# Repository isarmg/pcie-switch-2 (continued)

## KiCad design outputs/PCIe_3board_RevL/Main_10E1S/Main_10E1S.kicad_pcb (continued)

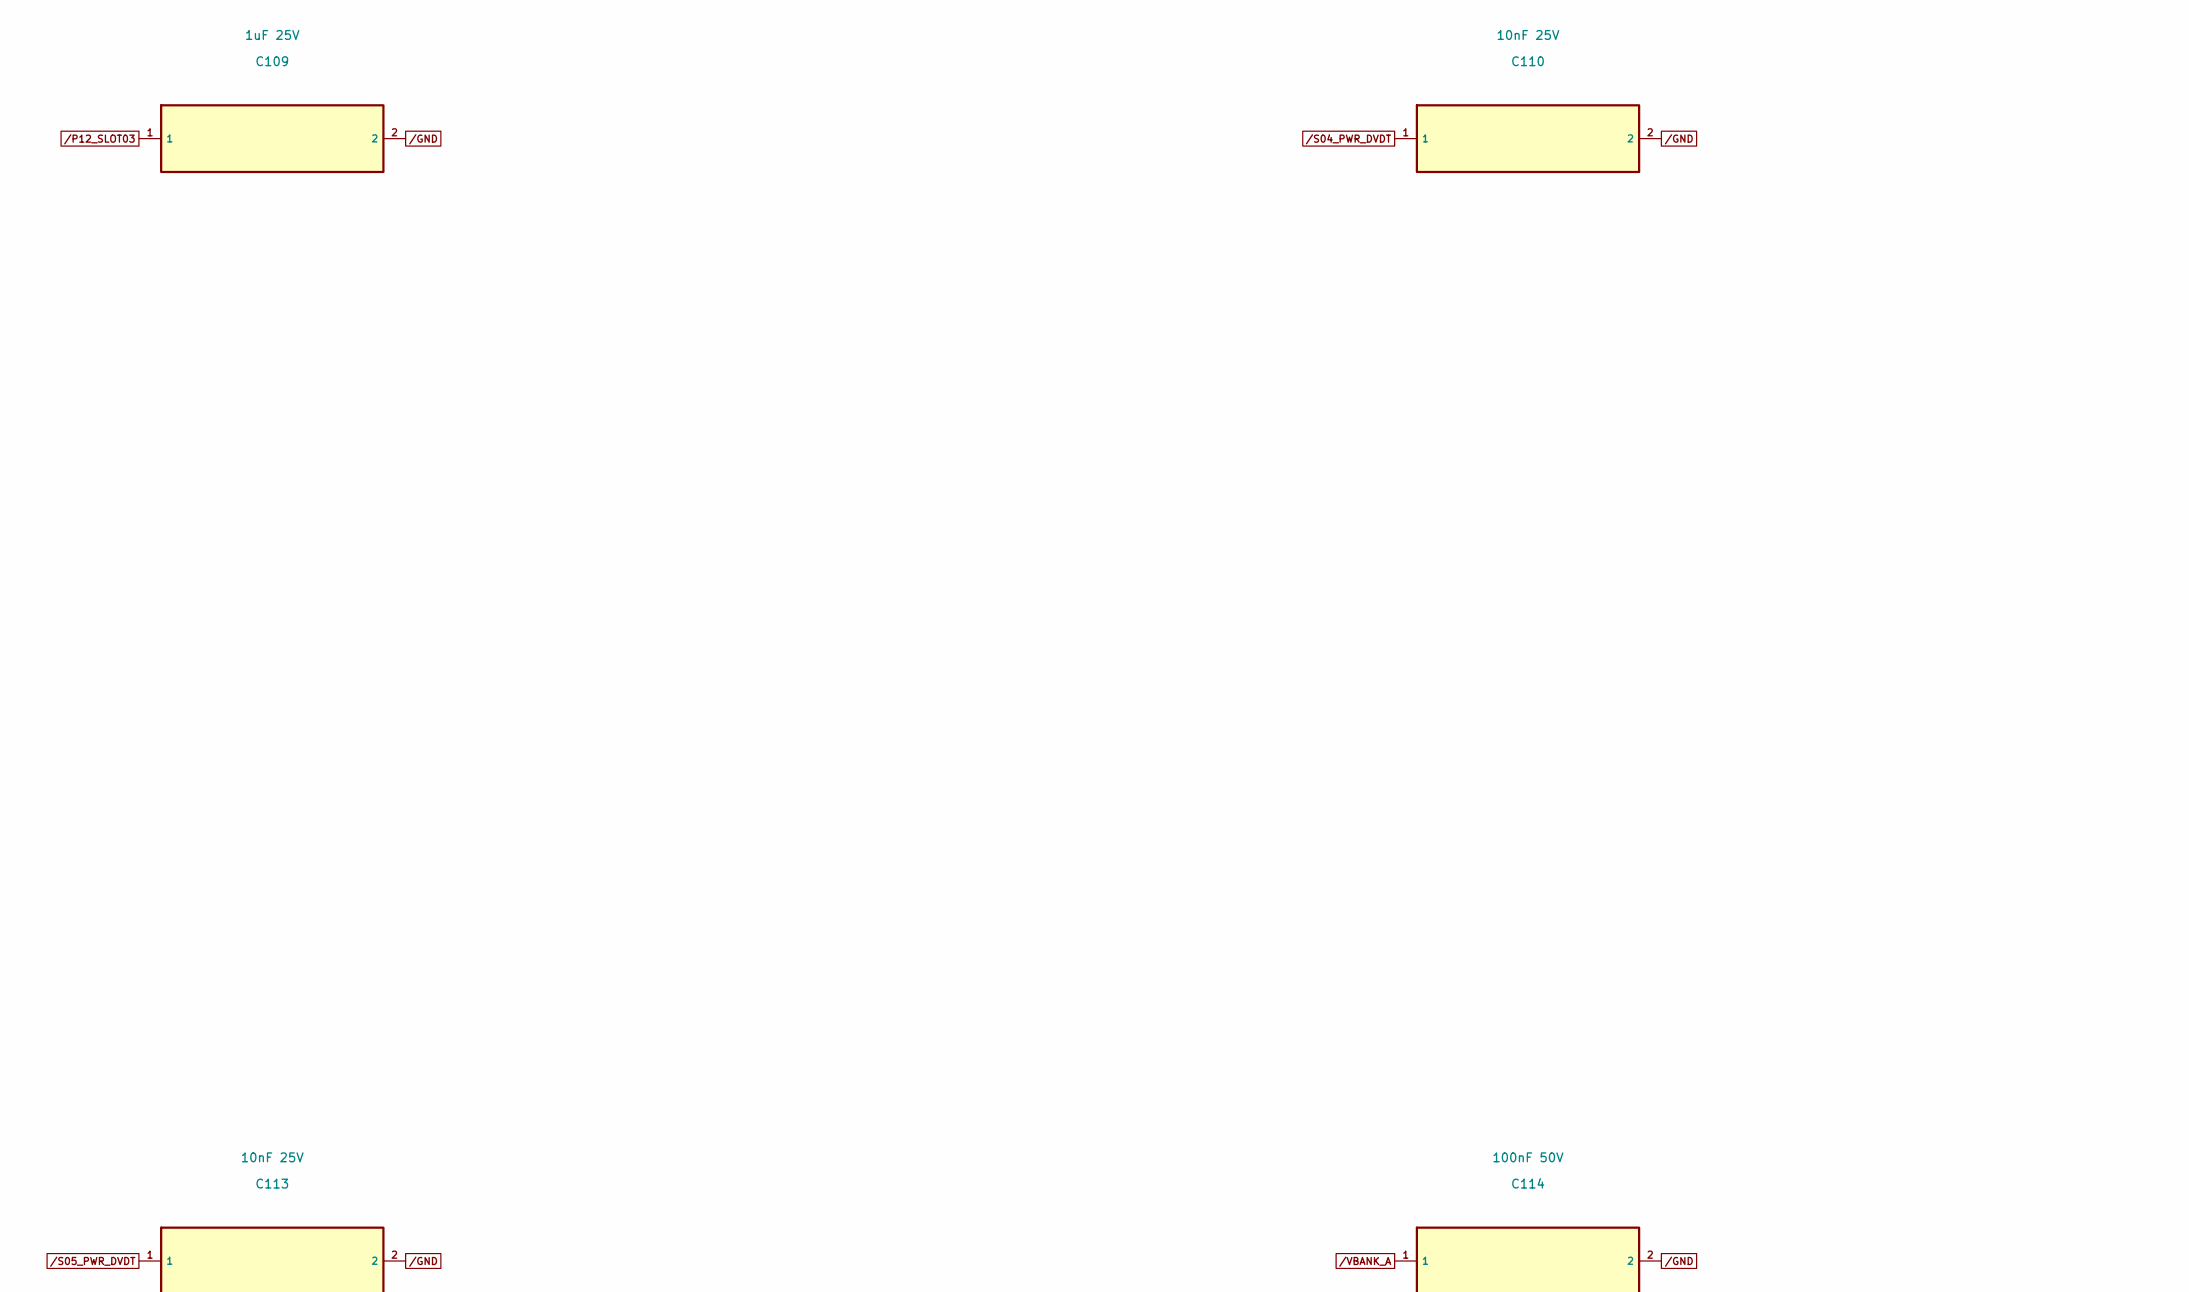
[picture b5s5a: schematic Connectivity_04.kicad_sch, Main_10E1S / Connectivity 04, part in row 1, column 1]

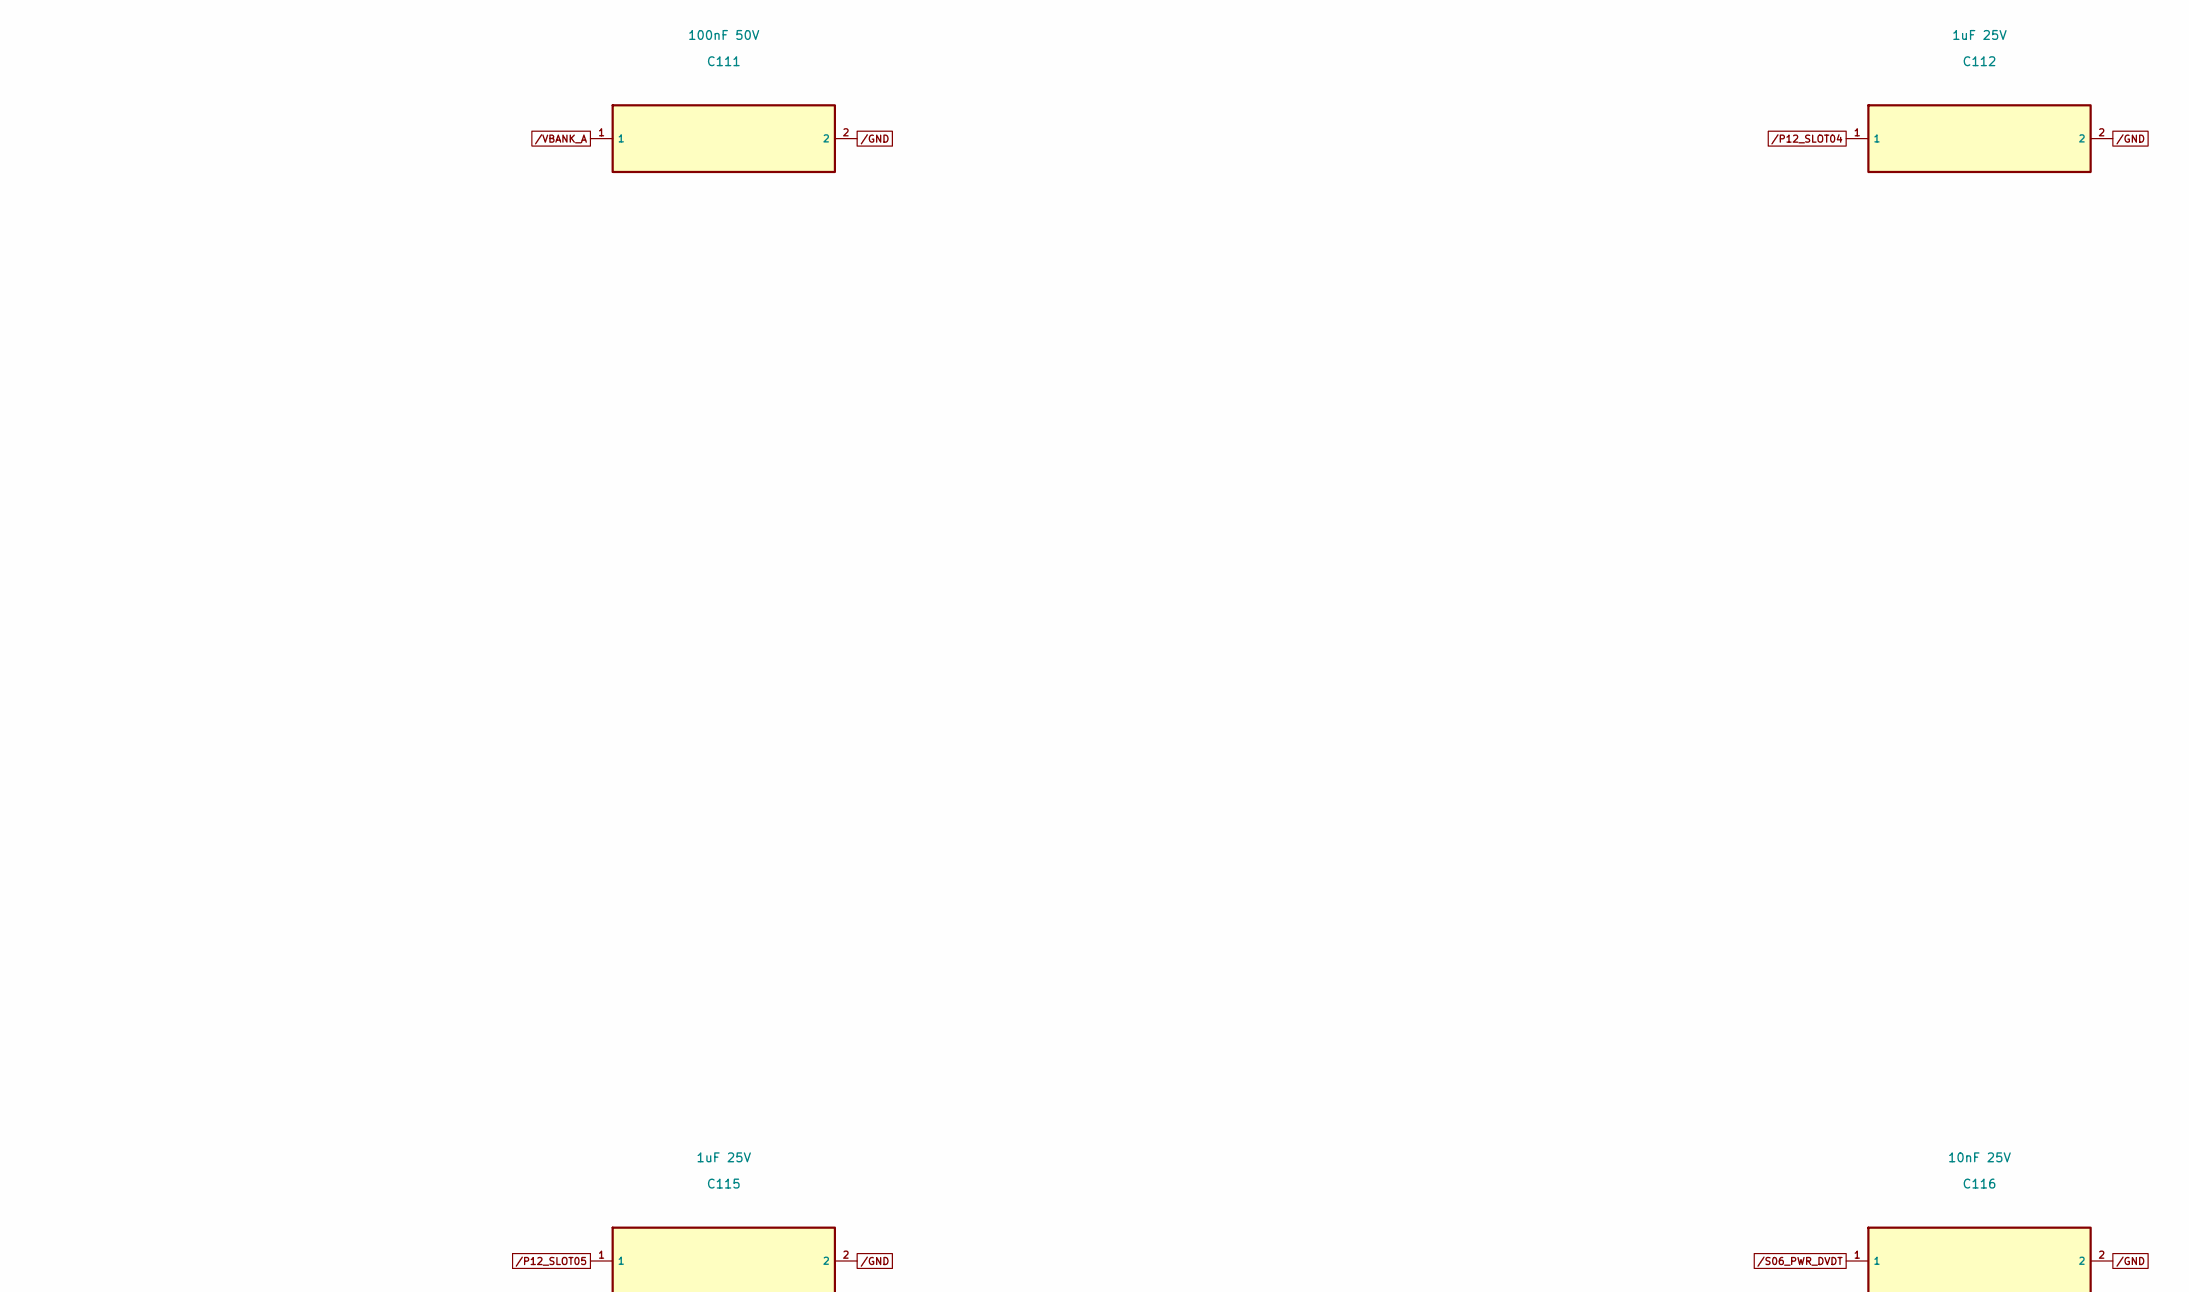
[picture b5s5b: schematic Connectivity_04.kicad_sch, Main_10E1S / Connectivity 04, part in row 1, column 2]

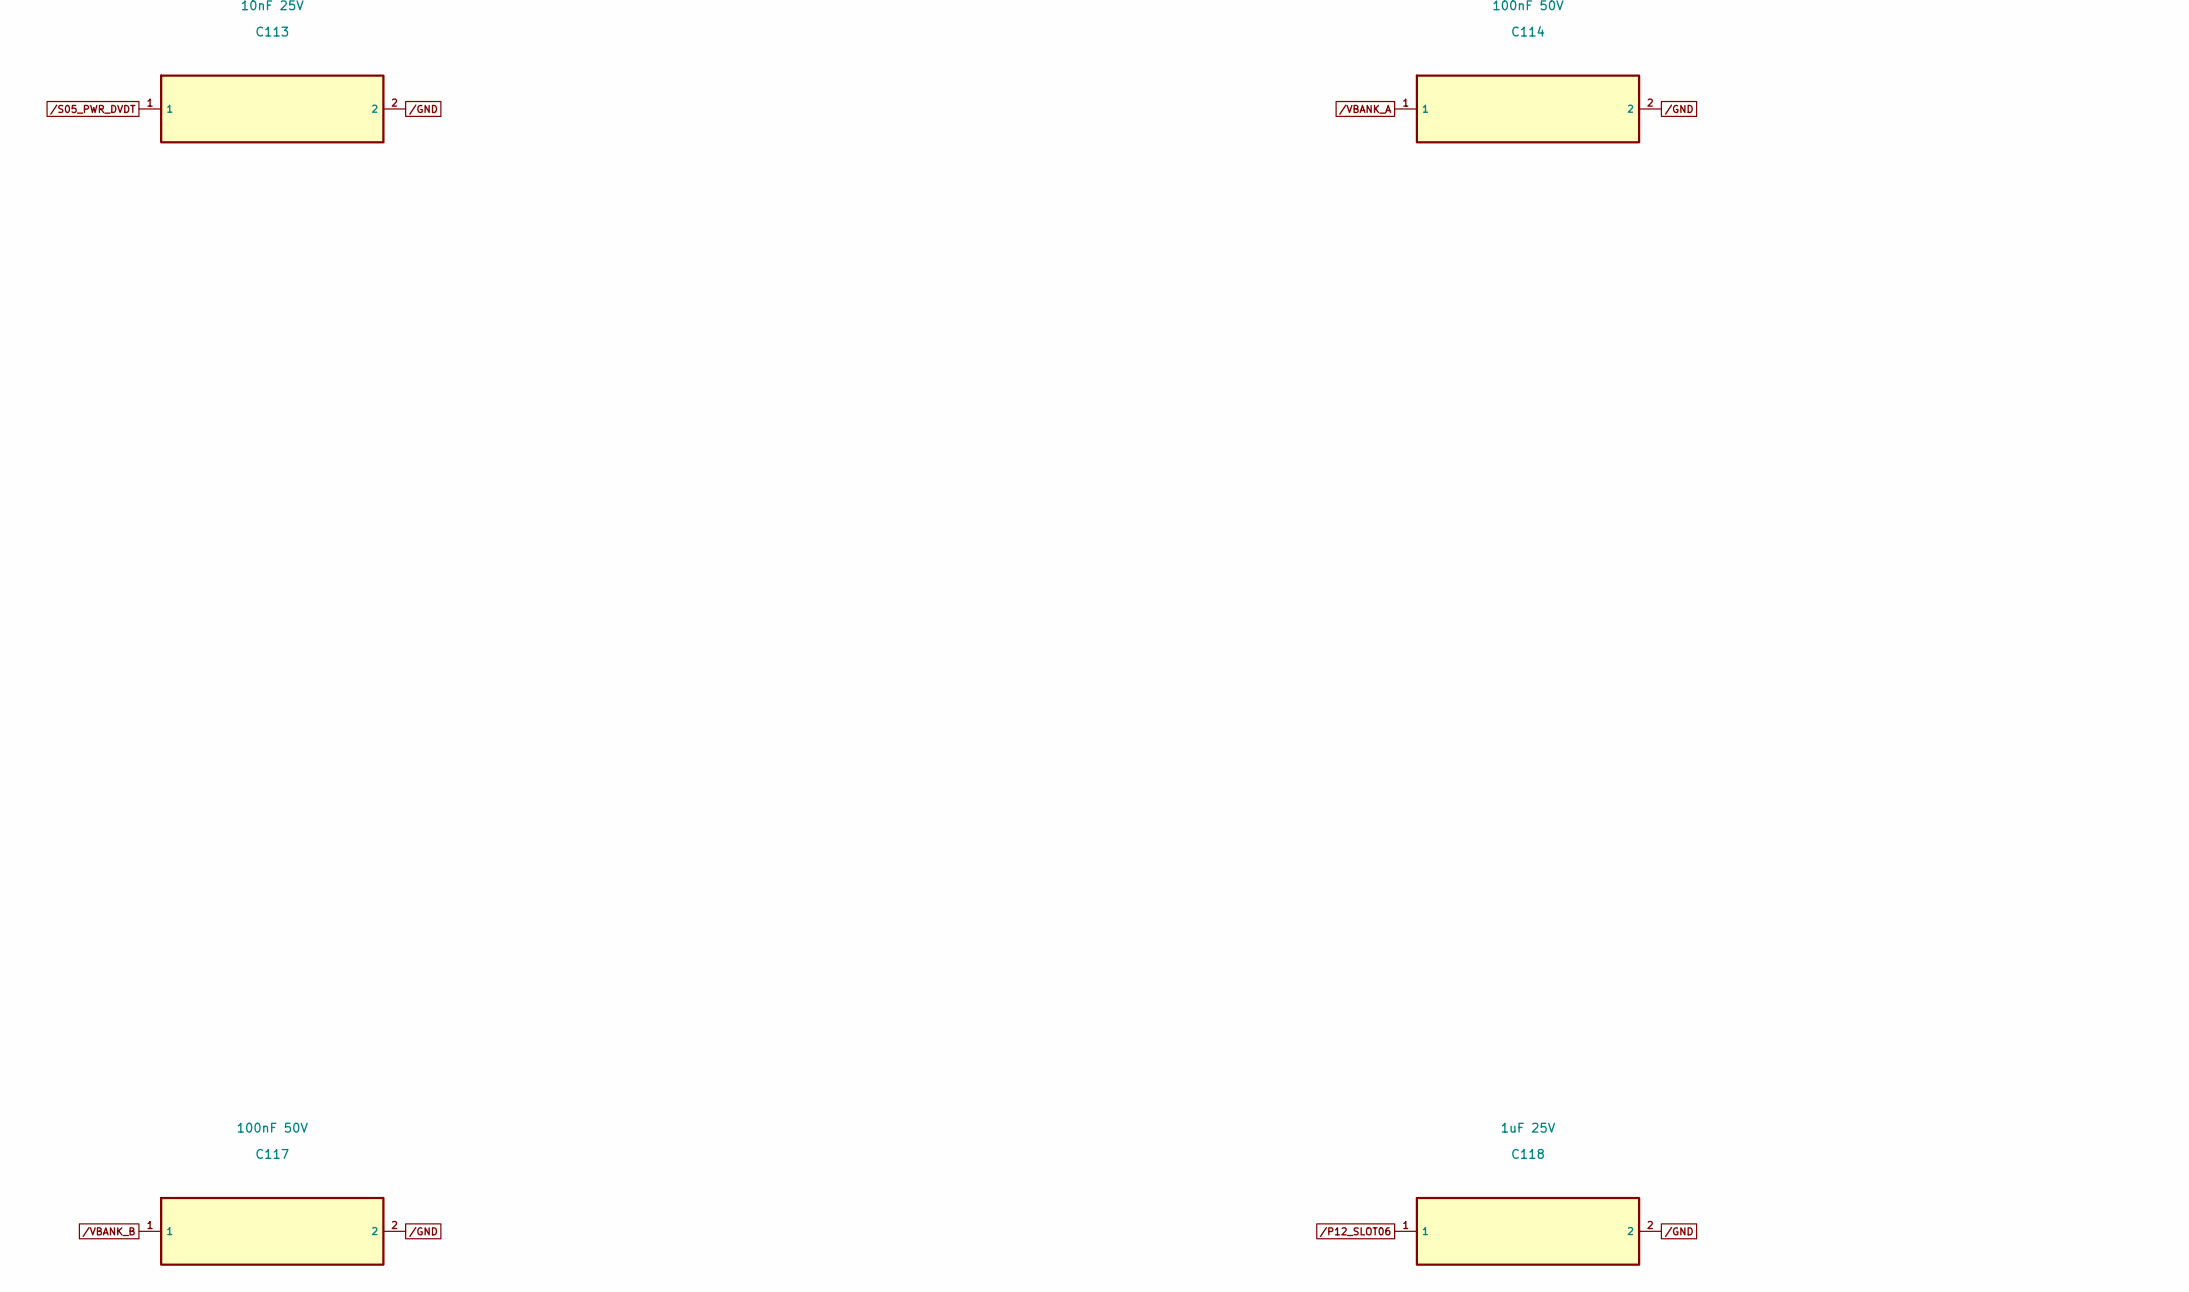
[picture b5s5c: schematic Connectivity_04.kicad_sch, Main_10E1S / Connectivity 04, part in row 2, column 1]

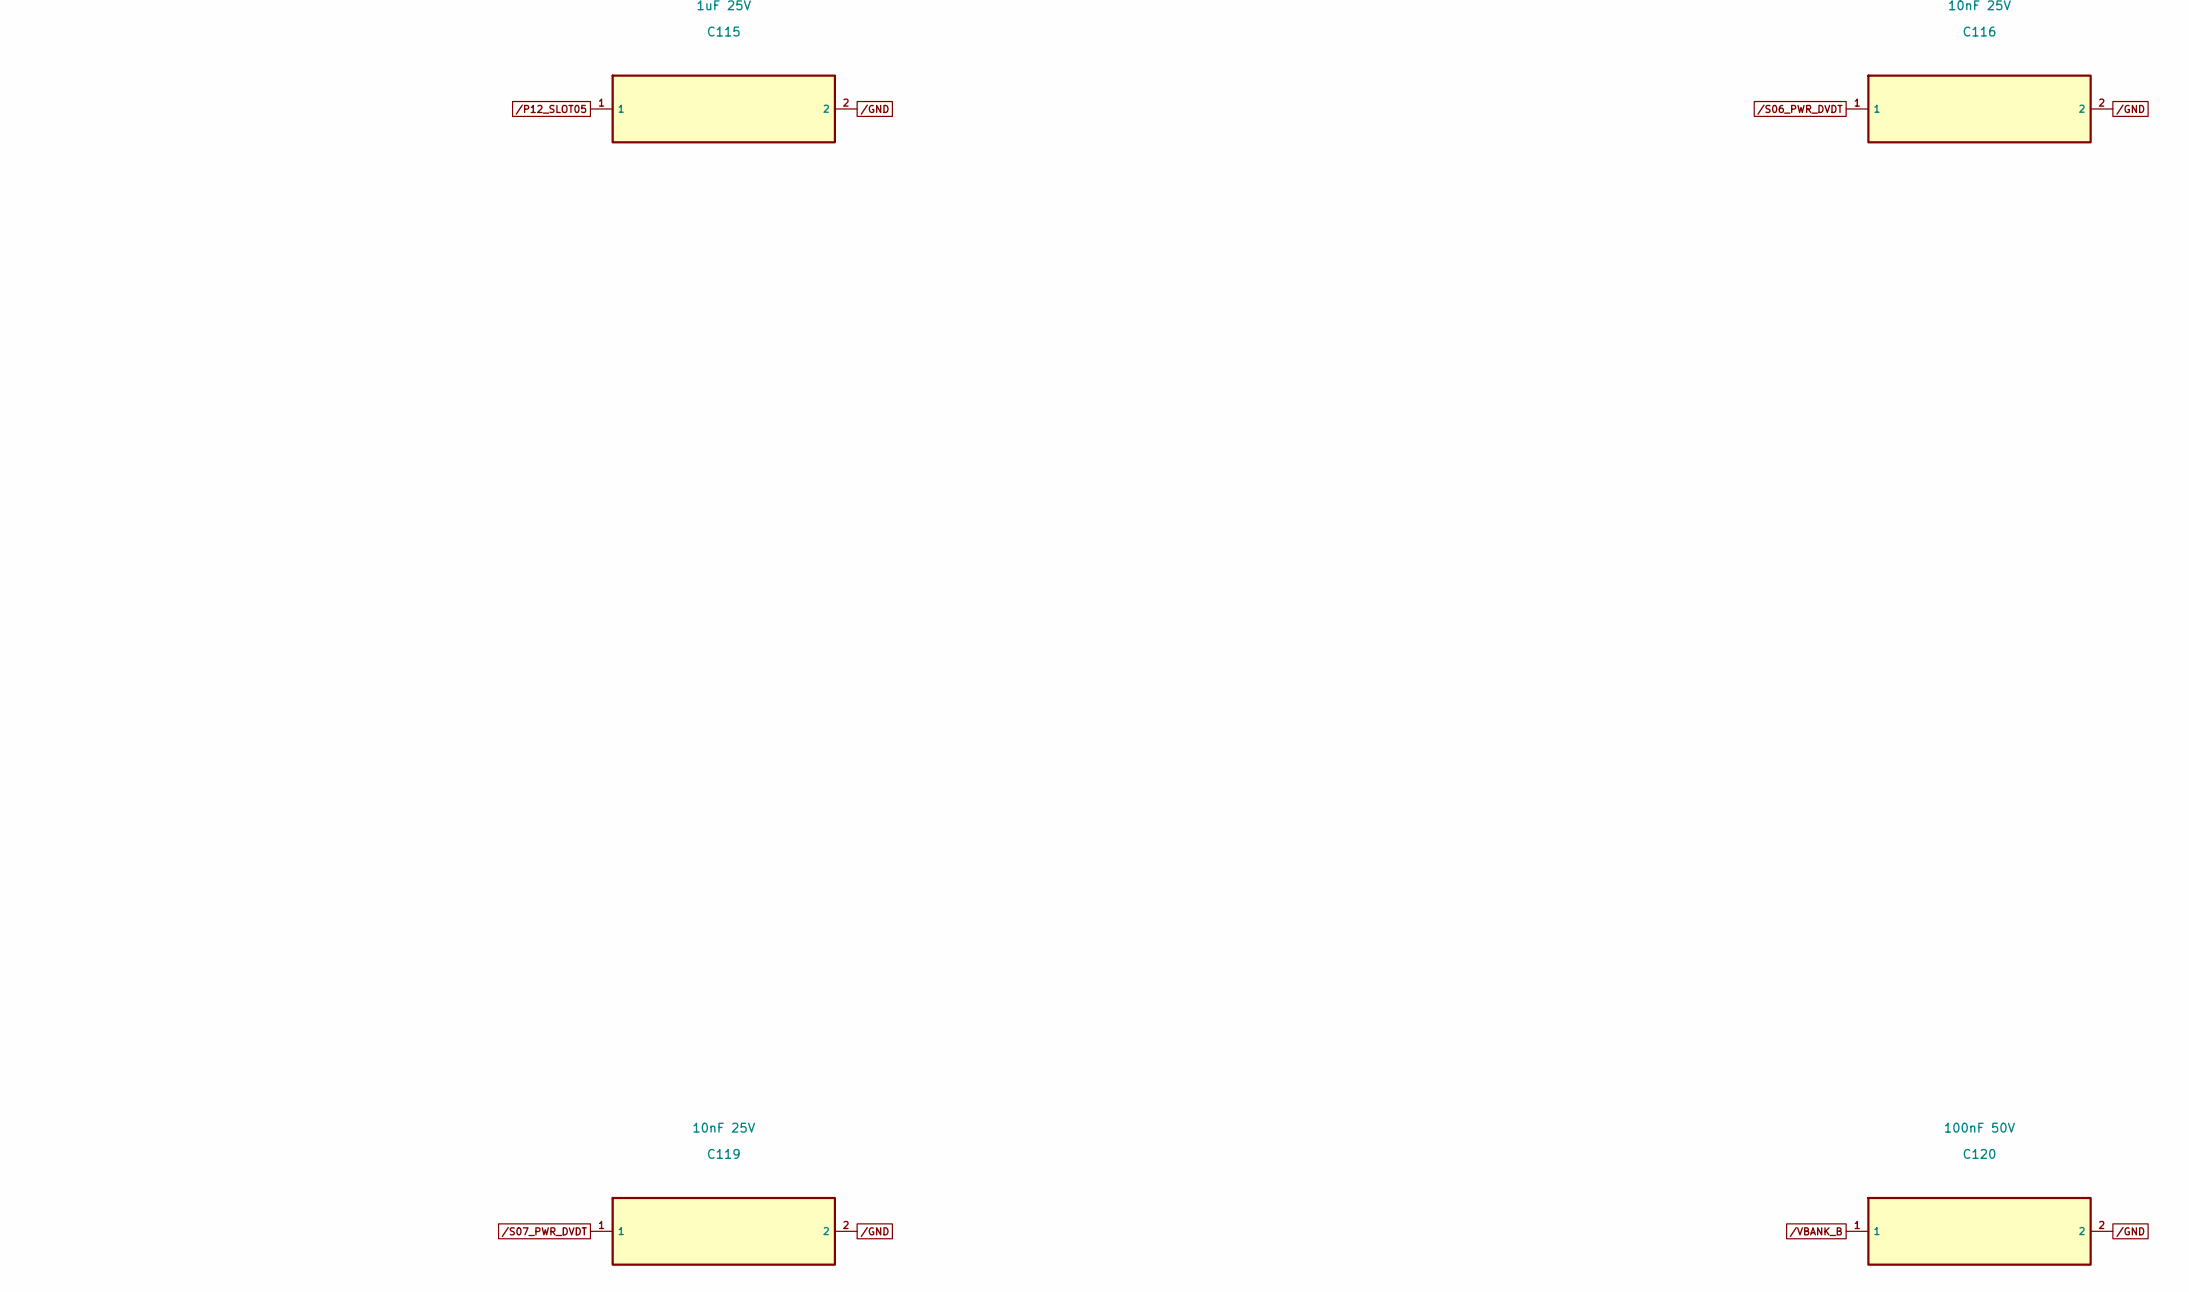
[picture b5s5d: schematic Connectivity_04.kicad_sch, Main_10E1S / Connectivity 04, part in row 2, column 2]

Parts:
C109, C112, C115, C118: 1uF 25V; C_0603_1608Metric
C110, C113, C116, C119: 10nF 25V; C_0402_1005Metric
C111, C114, C117, C120: 100nF 50V; C_0603_1608Metric

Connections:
/GND: C109.2, C110.2, C111.2, C112.2, C113.2, C114.2, C115.2, C116.2, C117.2, C118.2, C119.2, C120.2; also elsewhere on the board
/P12_SLOT03: C109.1; also elsewhere on the board
/P12_SLOT04: C112.1; also elsewhere on the board
/P12_SLOT05: C115.1; also elsewhere on the board
/P12_SLOT06: C118.1; also elsewhere on the board
/S04_PWR_DVDT: C110.1; also elsewhere on the board
/S05_PWR_DVDT: C113.1; also elsewhere on the board
/S06_PWR_DVDT: C116.1; also elsewhere on the board
/S07_PWR_DVDT: C119.1; also elsewhere on the board
/VBANK_A: C111.1, C114.1; also elsewhere on the board
/VBANK_B: C117.1, C120.1; also elsewhere on the board
